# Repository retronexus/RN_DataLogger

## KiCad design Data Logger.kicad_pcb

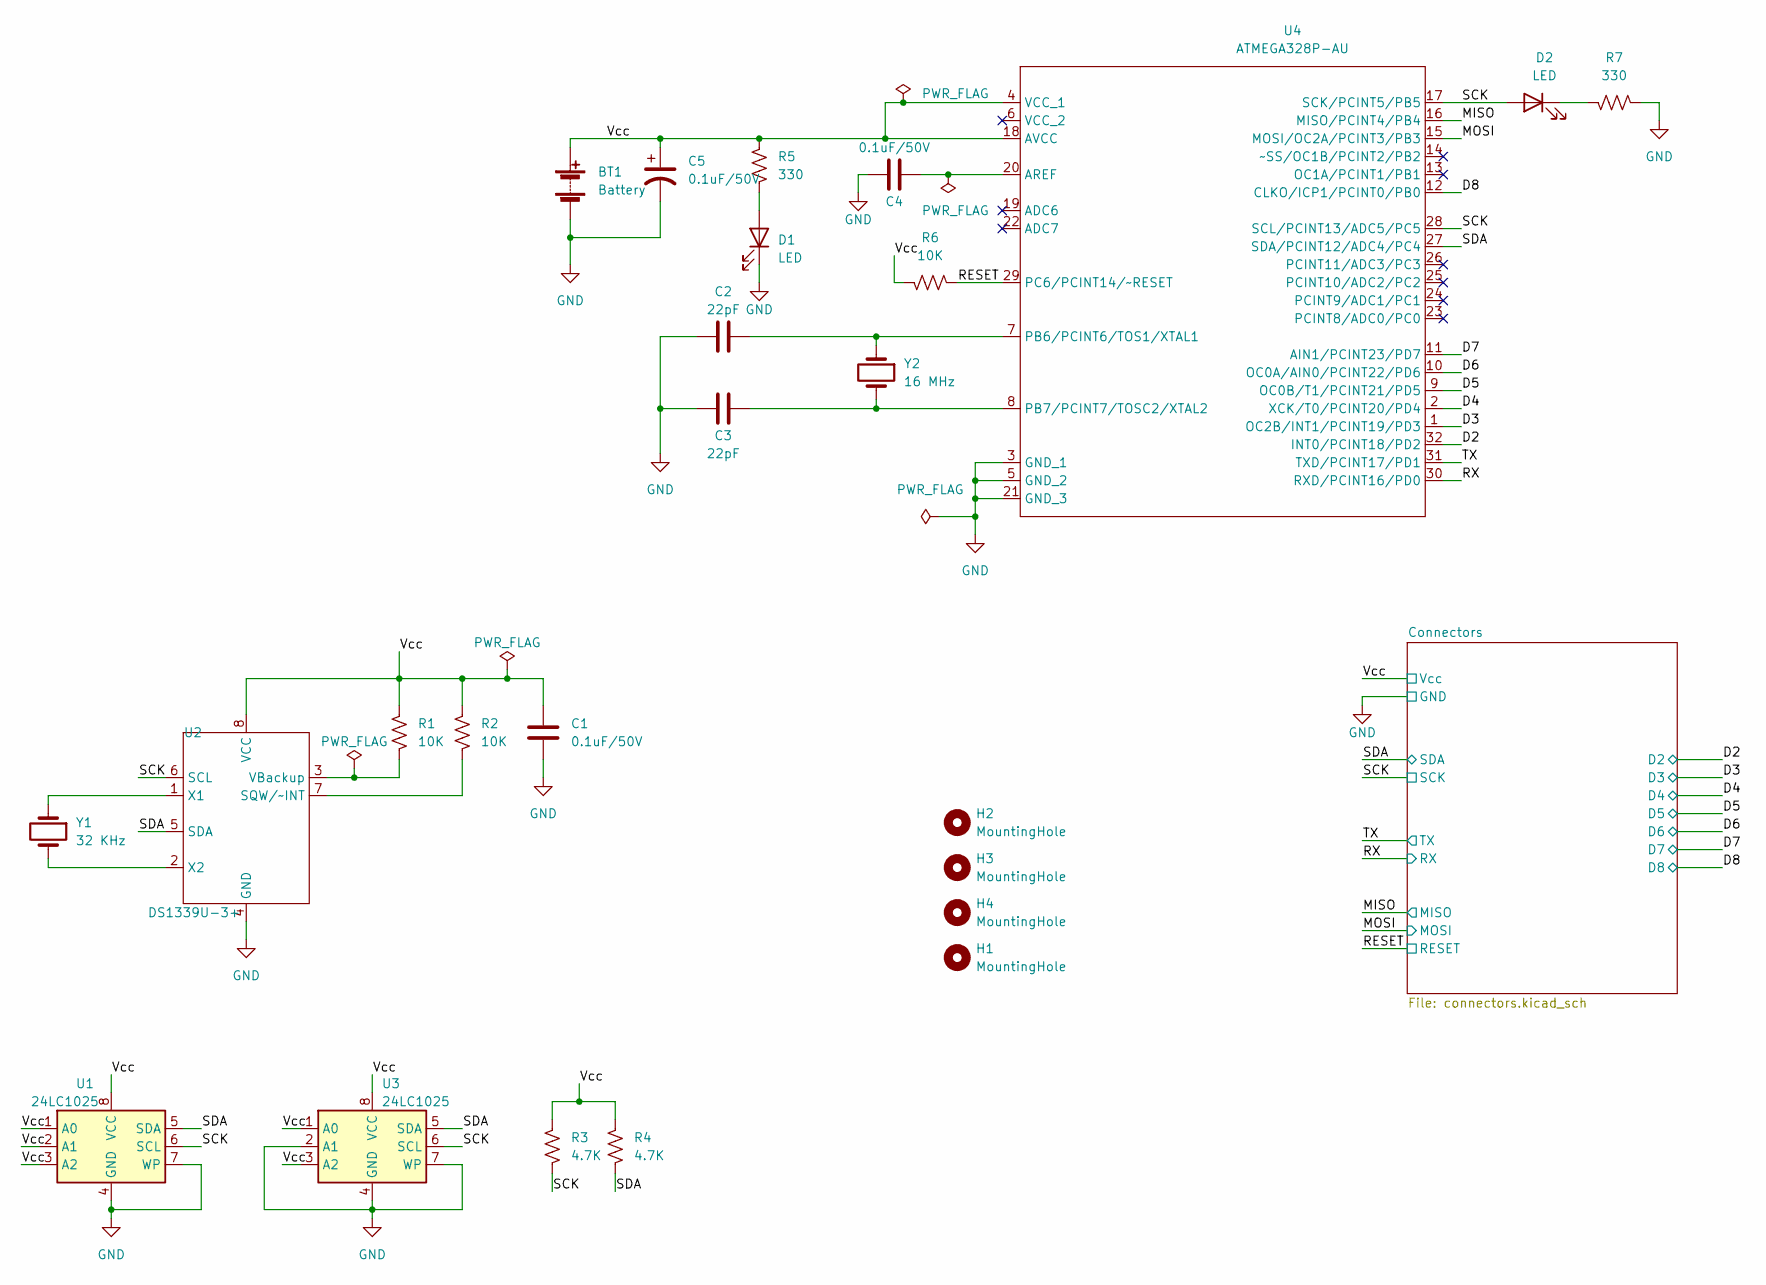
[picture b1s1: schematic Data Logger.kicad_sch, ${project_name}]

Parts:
BT1: Battery; J_PTH_CONN_HEADER_MALE_01x02_WUE_61300211121
C1, C4: 0.1uF/50V; C_SMD_0.1UF50V_0805_TDK_C2012X8R1H104K125AA
C2, C3: 22pF; C_SMD_22PF50V_0603_TDK_CGA3E2NP01H220J080AA
C5: 0.1uF/50V; C_POL_SMD_0.1UF50V_WUE_865230640001
D1, D2: LED; D_SMD_LED_GREEN_0805_WUE_150080GS75000
H1, H2, H3, H4: MountingHole; MOUNTINGHOLE_2.1MM
R1, R2, R6: 10K; R_SMD_10K_0805_YAG_RC0805FR-0710KL
R3, R4: 4.7K; R_SMD_4.7K_0805_YAG_RC0805FR-071KL
R5, R7: 330; R_SMD_330R_0805_YAG_RC0805FR-07330RL
U1, U3: 24LC1025; U_SMD_24LC1025_SOIC-08_MIC_24LC1025T-ESN
U2: DS1339U-3+; U_SMD_DS1339U_TSSOP08_ANA_DS1339U-3+
U4: ATMEGA328P-AU; U_SMD_ATMEGA320P-AU_QFP-32_MIC_ATMEGA328P-AU
Y1: 32 KHz; Y_SMD_CRYSTAL_32K_L5.0MMXW3.20_ABR_ABM3-32.000MHZ-D2Y-T
Y2: 16 MHz; Y_SMD_CRYSTAL_16K_L5.0MMXW3.20_ABR_ABM3-16.000MHZ-B2-T

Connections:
/D2: U4.32 (INT0/PCINT18/PD2); also elsewhere on the board
/D3: U4.1 (OC2B/INT1/PCINT19/PD3); also elsewhere on the board
/D4: U4.2 (XCK/T0/PCINT20/PD4); also elsewhere on the board
/D5: U4.9 (OC0B/T1/PCINT21/PD5); also elsewhere on the board
/D6: U4.10 (OC0A/AIN0/PCINT22/PD6); also elsewhere on the board
/D7: U4.11 (AIN1/PCINT23/PD7); also elsewhere on the board
/D8: U4.12 (CLKO/ICP1/PCINT0/PB0); also elsewhere on the board
/MISO: U4.16 (MISO/PCINT4/PB4); also elsewhere on the board
/MOSI: U4.15 (MOSI/OC2A/PCINT3/PB3); also elsewhere on the board
/RESET: R6.1, U4.29 (PC6/PCINT14/~RESET); also elsewhere on the board
/RX: U4.30 (RXD/PCINT16/PD0); also elsewhere on the board
/SCK: D2.2 (A), R3.2, U1.6 (SCL), U2.6 (SCL), U3.6 (SCL), U4.17 (SCK/PCINT5/PB5), U4.28 (SCL/PCINT13/ADC5/PC5); also elsewhere on the board
/SDA: R4.2, U1.5 (SDA), U2.5 (SDA), U3.5 (SDA), U4.27 (SDA/PCINT12/ADC4/PC4); also elsewhere on the board
/TX: U4.31 (TXD/PCINT17/PD1); also elsewhere on the board
/Vcc: BT1.1 (+), C1.1, C5.1, R1.2, R2.2, R3.1, R4.1, R5.2, R6.2, U1.1 (A0), U1.2 (A1), U1.3 (A2), U1.8 (VCC), U2.8 (VCC), U3.1 (A0), U3.3 (A2), U3.8 (VCC), U4.4 (VCC_1), U4.18 (AVCC); also elsewhere on the board
GND: BT1.2 (-), C1.2, C2.2, C3.1, C4.2, C5.2, D1.1 (K), R7.1, U1.4 (GND), U1.7 (WP), U2.4 (GND), U3.2 (A1), U3.4 (GND), U3.7 (WP), U4.3 (GND_1), U4.5 (GND_2), U4.21 (GND_3); also elsewhere on the board
unnamed: C2.1, U4.7 (PB6/PCINT6/TOS1/XTAL1), Y2.1
unnamed: C3.2, U4.8 (PB7/PCINT7/TOSC2/XTAL2), Y2.2
unnamed: C4.1, U4.20 (AREF)
unnamed: D1.2 (A), R5.1
unnamed: D2.1 (K), R7.2
unnamed: R1.1, U2.3 (VBackup)
unnamed: R2.1, U2.7 (SQW/~INT)
unnamed: U2.1 (X1), Y1.1
unnamed: U2.2 (X2), Y1.2

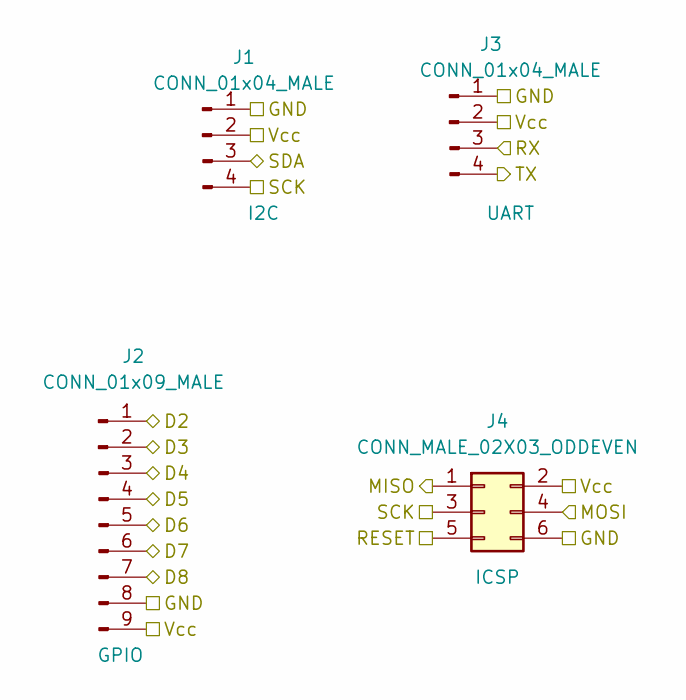
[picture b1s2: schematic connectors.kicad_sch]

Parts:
J1, J3: CONN_01x04_MALE; J_PTH_CONN_HEADER_MALE_01x04_WUE_61300411121
J2: CONN_01x09_MALE; J_PTH_CONN_HEADER_MALE_01x09_WUE_61300911121
J4: CONN_MALE_02X03_ODDEVEN; J_PTH_CONN_HEADER_MALE_02x03_WUE_61300621121

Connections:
/D2: J2.1; also elsewhere on the board
/D3: J2.2; also elsewhere on the board
/D4: J2.3; also elsewhere on the board
/D5: J2.4; also elsewhere on the board
/D6: J2.5; also elsewhere on the board
/D7: J2.6; also elsewhere on the board
/D8: J2.7; also elsewhere on the board
/MISO: J4.1; also elsewhere on the board
/MOSI: J4.4; also elsewhere on the board
/RESET: J4.5; also elsewhere on the board
/RX: J3.3; also elsewhere on the board
/SCK: J1.4, J4.3; also elsewhere on the board
/SDA: J1.3; also elsewhere on the board
/TX: J3.4; also elsewhere on the board
/Vcc: J1.2, J2.9, J3.2, J4.2; also elsewhere on the board
GND: J1.1, J2.8, J3.1, J4.6; also elsewhere on the board

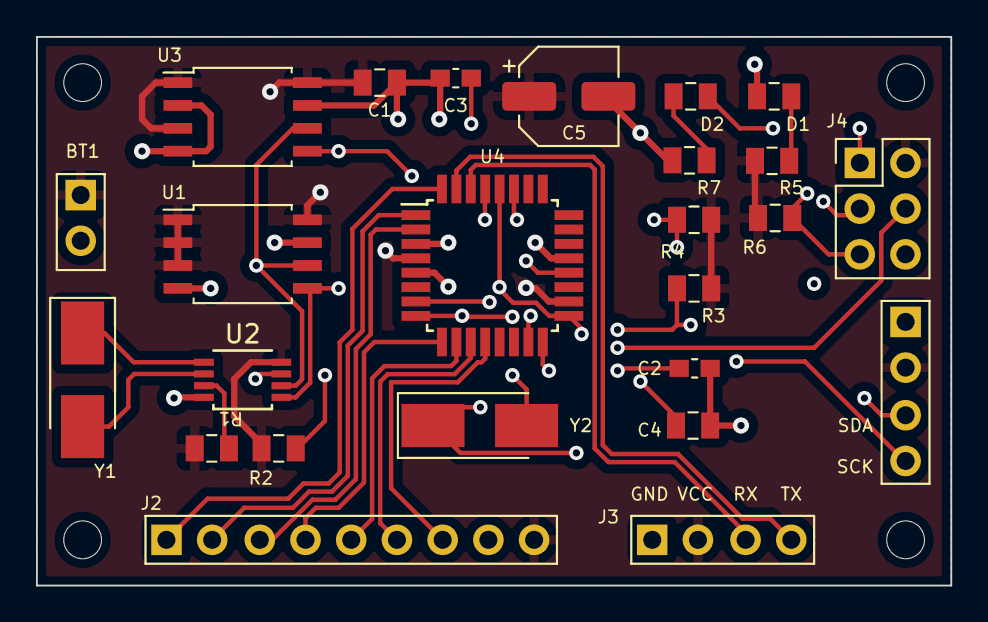
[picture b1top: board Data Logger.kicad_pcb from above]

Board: 4 copper layers, 50.8 x 30.5 mm, 29 parts (0 on the bottom side), 25 nets.

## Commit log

2022-06-05 Completed Symbol to footprint associations
2022-06-11 update schematics
2022-06-11 update pcb
2022-07-03 Completed Routing
2022-07-03 Silkscreen Adjustment
2022-07-03 Fixed Routing
2022-07-03 routing
